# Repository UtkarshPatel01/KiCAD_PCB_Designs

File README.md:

# 🚀KiCAD PCB Designs✨
This repository contains PCB Designs createed on KiCAD with their gerber files.
<br>
<br>
<br>

## Author: Utkarsh Patel🔥

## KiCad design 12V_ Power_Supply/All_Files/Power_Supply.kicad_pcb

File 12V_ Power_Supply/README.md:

# 🚀12V Power Supply✨
This repository contains all the files (including gerber files) and Schematics.
<br>
<br>
<br>
# 👉🏻⚠️NOTE: Kindly verify schematic and layout before using it blindly in your project.
<br>
<br>
## Author: Utkarsh Patel🔥

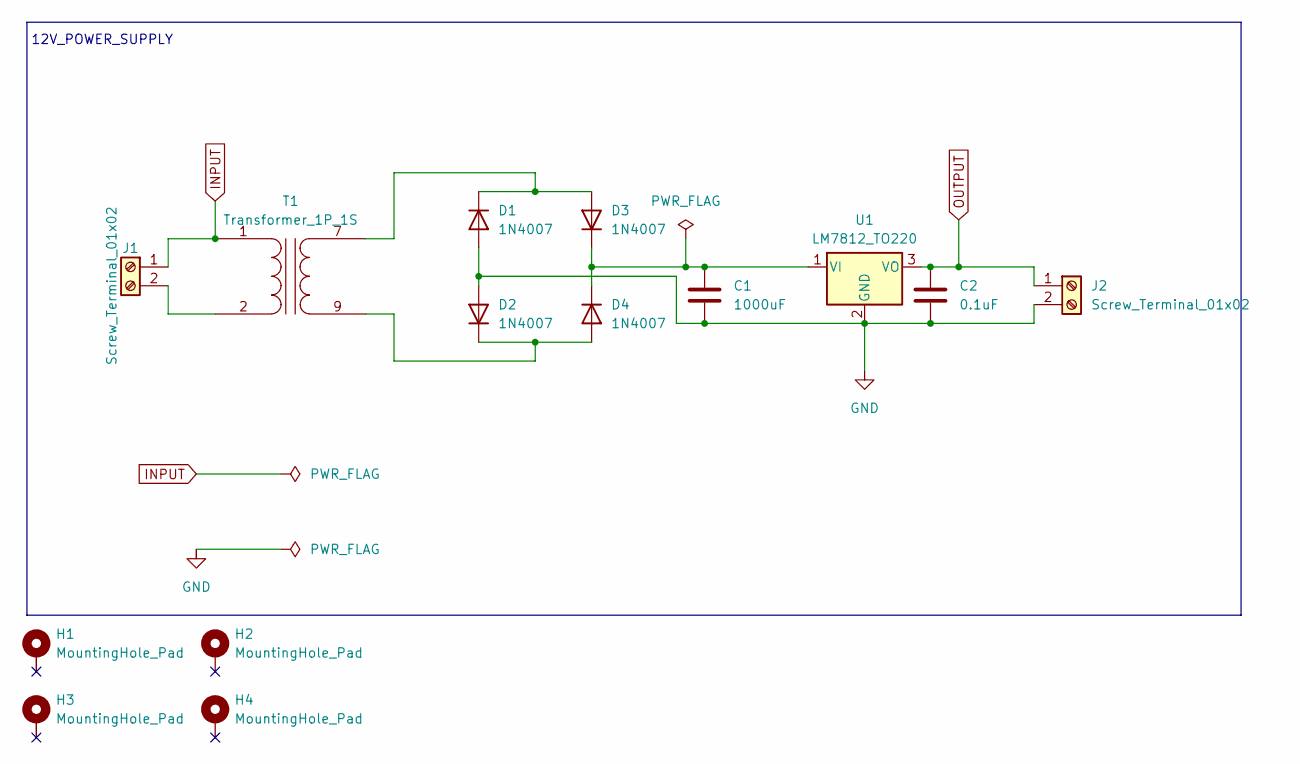
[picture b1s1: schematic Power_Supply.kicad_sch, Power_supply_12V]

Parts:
C1: 1000uF; C_1210_3225Metric
C2: 0.1uF; C_1206_3216Metric
D1, D2, D3, D4: 1N4007; D_DO-41_SOD81_P10.16mm_Horizontal
H1, H2, H3, H4: MountingHole_Pad; MountingHole_2.2mm_M2_Pad_Via
J1, J2: Screw_Terminal_01x02; TerminalBlock_bornier-2_P5.08mm
T1: Transformer_1P_1S; Transformer_NF_ETAL_P3356
U1: LM7812_TO220; TO-220-3_Vertical

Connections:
GND: C1.2, C2.2, D1.2 (A), D2.2 (A), J2.2, U1.2 (GND)
INPUT: J1.1, T1.1 (AA)
unnamed: D1.1 (K), D3.2 (A), T1.7 (SB)
unnamed: D2.1 (K), D4.2 (A), T1.9 (SA)
unnamed: C1.1, D3.1 (K), D4.1 (K), U1.1 (VI)
unnamed: J1.2, T1.2 (AB)
OUTPUT: C2.1, J2.1, U1.3 (VO)

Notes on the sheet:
12V_POWER_SUPPLY

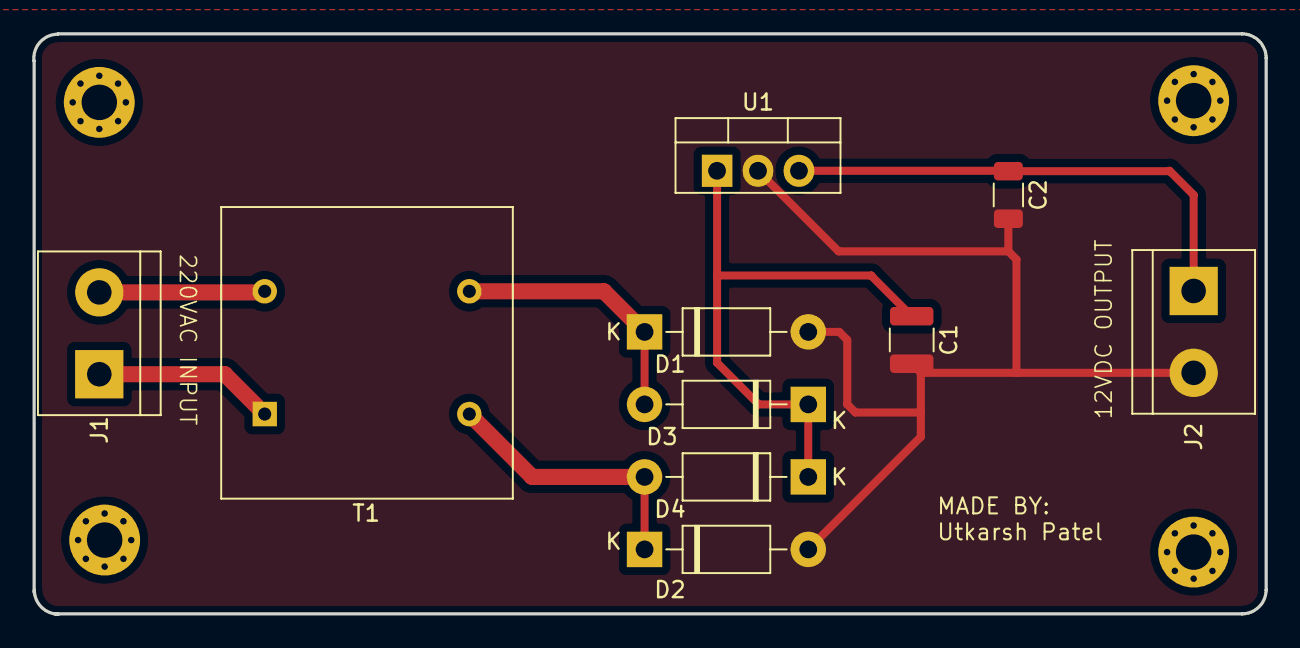
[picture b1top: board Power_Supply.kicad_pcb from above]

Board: 2 copper layers, 76.5 x 36.0 mm, 14 parts (0 on the bottom side), 7 nets.

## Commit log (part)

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2025-08-07 README.md
2025-08-07 This Include all Gerber Files
2025-08-07 Other Files
2025-08-07 Schematic Diagram
2025-08-07 Schematic_Diagram.png
2025-08-07 PCB Layout
2025-08-07 PCB Layout.png
2025-08-07 PCB Layout close look
2025-08-07 PCB Layout close look.png
2025-08-07 3D PCB Design
    3D PCB Design
2025-08-07 3D PCB Design3.png
2025-08-07 3D PCB Design1.png
2025-08-07 3D PCB Design2.png
